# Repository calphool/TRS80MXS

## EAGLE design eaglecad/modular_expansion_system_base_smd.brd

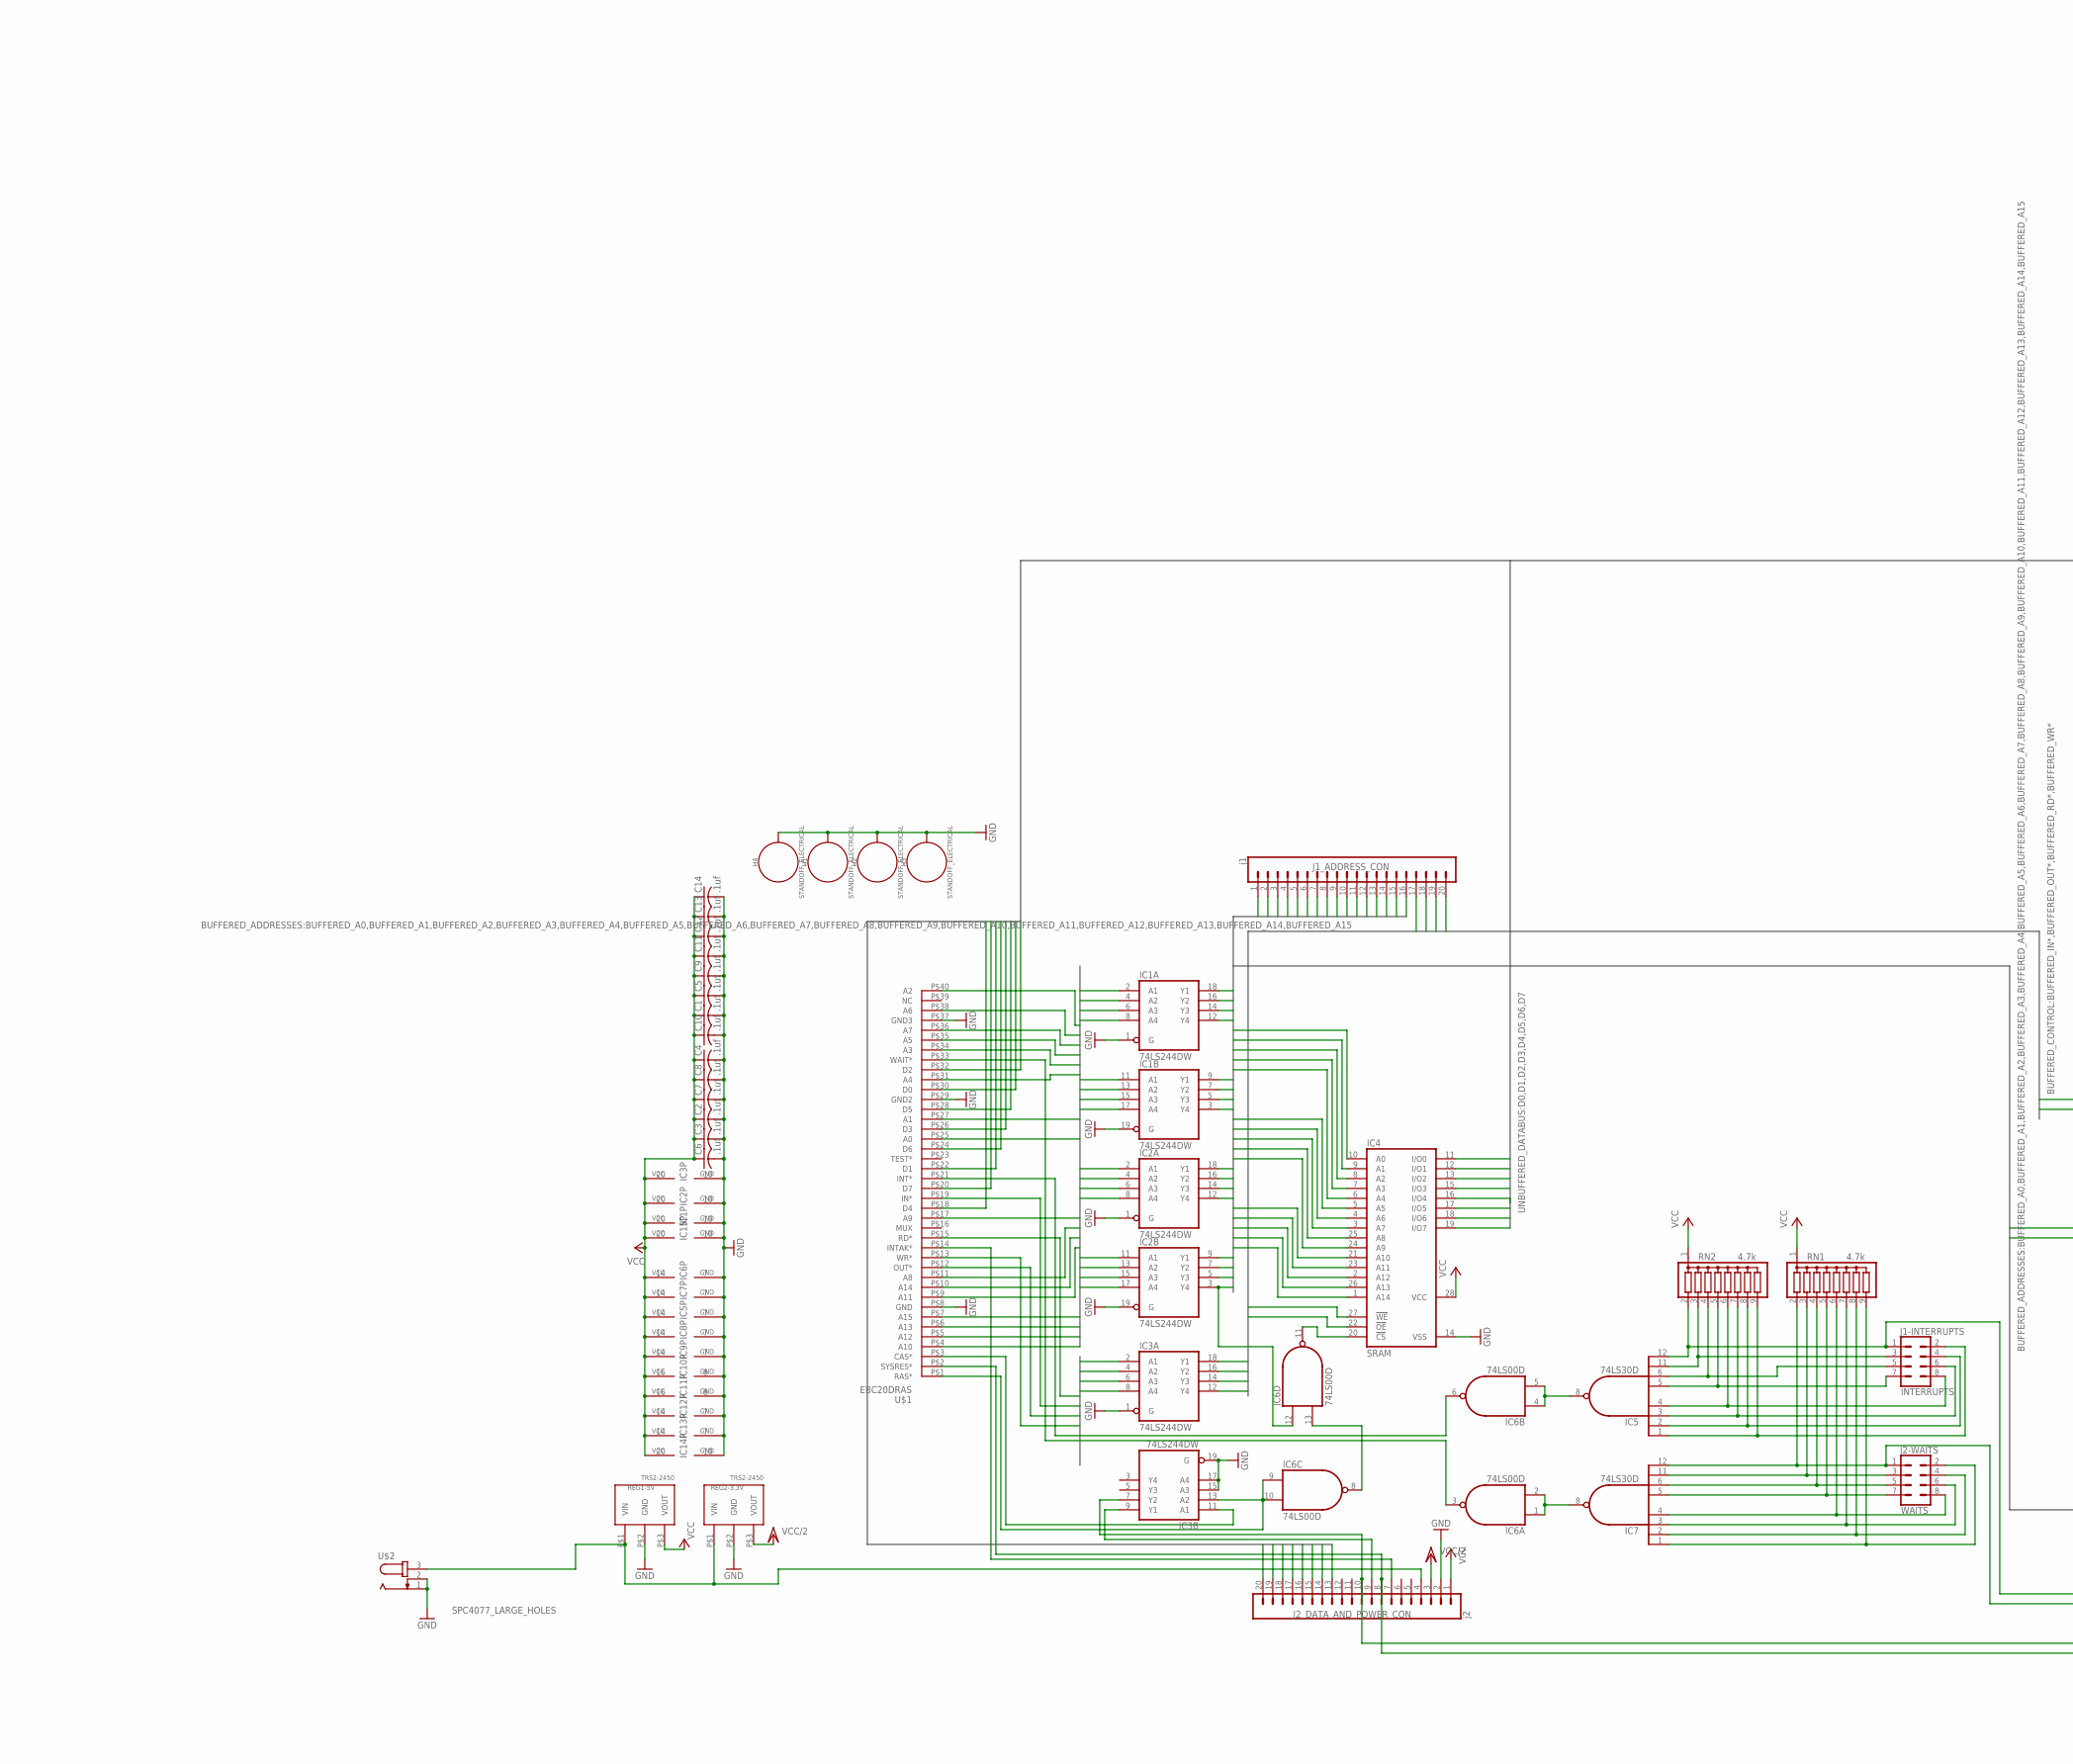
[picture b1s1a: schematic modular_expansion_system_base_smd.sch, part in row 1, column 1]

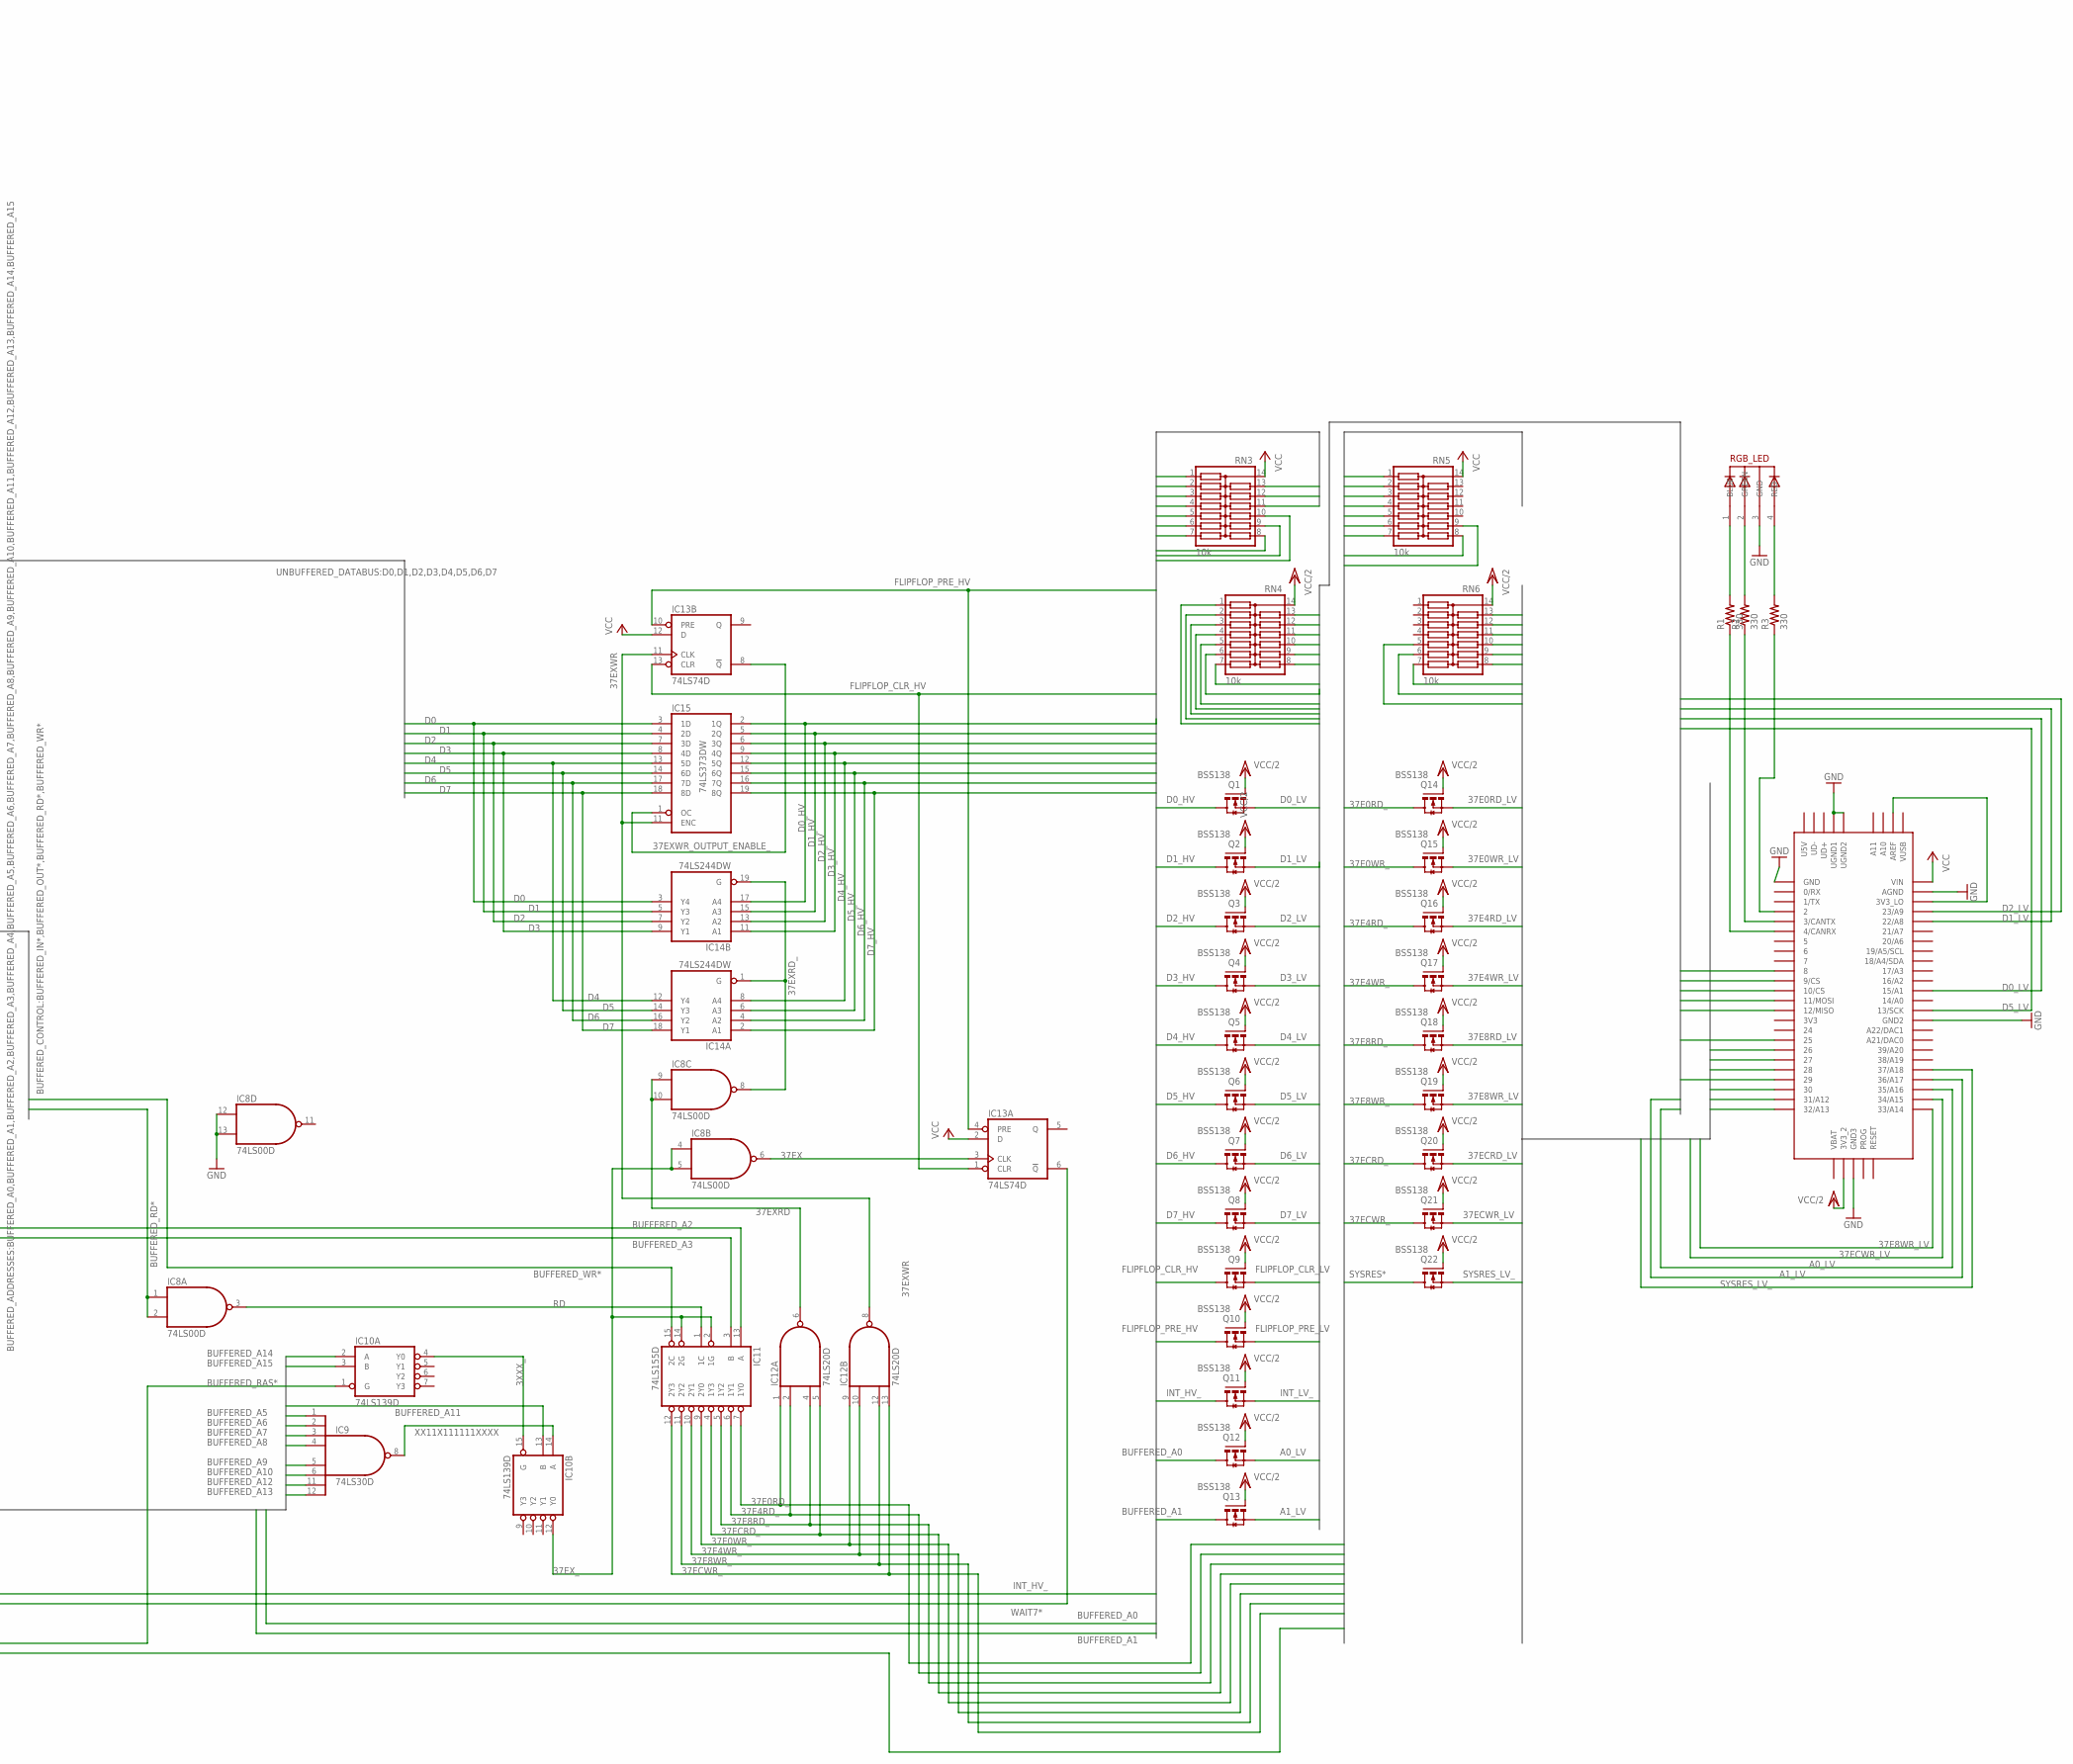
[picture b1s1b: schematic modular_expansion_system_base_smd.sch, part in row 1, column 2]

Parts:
C1, C2, C3, C4, C5, C6, C7, C8, C9, C10, C11, C12, C13, C14: .1uf; C025-025X050
H1, H2, H3, H4: STANDOFF_ELECTRICAL; STANDOFF-ELECTRICAL
IC1, IC2, IC3, IC14: 74LS244DW; SO20W
IC4: SRAM; SO28L
IC5, IC7, IC9: 74LS30D; SO14
IC6, IC8: 74LS00D; SO14
IC10: 74LS139D; SO16
IC11: 74LS155D; SO16
IC12: 74LS20D; SO14
IC13: 74LS74D; SO14
IC15: 74LS373DW; SO20W
J1-INTERRUPTS: INTERRUPTS; 2X4
J1_ADDRESS_CON: j1; 1X20
J2-WAITS: WAITS; 2X4
J2_DATA_AND_POWER_CON: j2; 1X20
Q1, Q2, Q3, Q4, Q5, Q6, Q7, Q8, Q9, Q10, Q11, Q12, Q13, Q14, Q15, Q16, Q17, Q18, Q19, Q20, Q21, Q22: BSS138; SOT23-3
R1, R2, R3: 330; 0207/2V
REG1-5V, REG2-3.3V: TRS2-2450; TRACON_REG
RGB_LED: 5MMRGBLED; LED5MMRGB
RN1, RN2: 4.7k; SIL9
RN3, RN4, RN5, RN6: 10k; SOMC14
U$1: EBC20DRAS
U$2: SPC4077_LARGE_HOLES; SPC4077
U$3: TEENSY_3.5/3.6

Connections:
3XXX_: IC10.4 (Y0), IC10.15 (G)
9V-IN: J2_DATA_AND_POWER_CON.4, REG1-5V.P$1 (VIN), REG2-3.3V.P$1 (VIN), U$2.3
37E0RD_: IC11.7 (1Y0), IC12.1 (I0), Q14.3 (D), RN5.1
37E0RD_LV: Q14.2 (S), RN6.13, U$3.31/A12
37E0WR_: IC11.9 (2Y0), IC12.9 (I0), Q15.3 (D), RN5.2
37E0WR_LV: Q15.2 (S), RN6.12, U$3.27
37E4RD_: IC11.6 (1Y1), IC12.2 (I1), Q16.3 (D), RN5.3
37E4RD_LV: Q16.2 (S), RN6.11, U$3.32/A13
37E4WR_: IC11.10 (2Y1), IC12.10 (I1), Q17.3 (D), RN5.4
37E4WR_LV: Q17.2 (S), RN6.10, U$3.28
37E8RD_: IC11.5 (1Y2), IC12.4 (I2), Q18.3 (D), RN5.5
37E8RD_LV: Q18.2 (S), RN6.9, U$3.30
37E8WR_: IC11.11 (2Y2), IC12.12 (I2), Q19.3 (D), RN5.6
37E8WR_LV: Q19.2 (S), RN6.8, U$3.33/A14
37ECRD_: IC11.4 (1Y3), IC12.5 (I3), Q20.3 (D), RN5.7
37ECRD_LV: Q20.2 (S), RN6.7, U$3.26
37ECWR_: IC11.12 (2Y3), IC12.13 (I3), Q21.3 (D), RN5.8
37ECWR_LV: Q21.2 (S), RN6.6, U$3.34/A15
37EX: IC8.6 (O), IC13.3 (CLK)
37EXRD: IC8.9 (I0), IC8.10 (I1), IC12.6 (O)
37EXRD_: IC8.8 (O), IC14.1 (G), IC14.19 (G)
37EXWR: IC12.8 (O), IC13.11 (CLK), IC15.11 (ENC)
37EXWR_OUTPUT_ENABLE_: IC13.8 (!Q), IC15.1 (OC)
37EX_: IC8.4 (I0), IC8.5 (I1), IC10.12 (Y0), IC11.2 (1G), IC11.14 (2G)
A0: IC1.2 (A1), U$1.P$25 (A0)
A0_LV: Q12.2 (S), RN4.2, U$3.35/A16
A1: IC1.4 (A2), U$1.P$27 (A1)
A1_LV: Q13.2 (S), RN4.1, U$3.36/A17
A2: IC1.6 (A3), U$1.P$40 (A2)
A3: IC1.8 (A4), U$1.P$34 (A3)
A4: IC1.11 (A1), U$1.P$31 (A4)
A5: IC1.13 (A2), U$1.P$35 (A5)
A6: IC1.15 (A3), U$1.P$38 (A6)
A7: IC1.17 (A4), U$1.P$36 (A7)
A8: IC2.2 (A1), U$1.P$11 (A8)
A9: IC2.4 (A2), U$1.P$17 (A9)
A10: IC2.6 (A3), U$1.P$4 (A10)
A11: IC2.8 (A4), U$1.P$9 (A11)
A12: IC2.11 (A1), U$1.P$5 (A12)
A13: IC2.13 (A2), U$1.P$6 (A13)
A14: IC2.15 (A3), U$1.P$10 (A14)
A15: IC2.17 (A4), U$1.P$7 (A15)
A15_AND_RAS: IC4.20 (!CS), IC6.11 (O)
BUFFERED_A0: IC1.18 (Y1), IC4.10 (A0), J1_ADDRESS_CON.1, Q12.3 (D), RN3.12
BUFFERED_A1: IC1.16 (Y2), IC4.9 (A1), J1_ADDRESS_CON.2, Q13.3 (D), RN3.13
BUFFERED_A2: IC1.14 (Y3), IC4.8 (A2), IC11.13 (A), J1_ADDRESS_CON.3
BUFFERED_A3: IC1.12 (Y4), IC4.7 (A3), IC11.3 (B), J1_ADDRESS_CON.4
BUFFERED_A4: IC1.9 (Y1), IC4.6 (A4), J1_ADDRESS_CON.5
BUFFERED_A5: IC1.7 (Y2), IC4.5 (A5), IC9.1 (I0), J1_ADDRESS_CON.6
BUFFERED_A6: IC1.5 (Y3), IC4.4 (A6), IC9.2 (I1), J1_ADDRESS_CON.7
BUFFERED_A7: IC1.3 (Y4), IC4.3 (A7), IC9.3 (I2), J1_ADDRESS_CON.8
BUFFERED_A8: IC2.18 (Y1), IC4.25 (A8), IC9.4 (I3), J1_ADDRESS_CON.9
BUFFERED_A9: IC2.16 (Y2), IC4.24 (A9), IC9.5 (I4), J1_ADDRESS_CON.10
BUFFERED_A10: IC2.14 (Y3), IC4.21 (A10), IC9.6 (I5), J1_ADDRESS_CON.11
BUFFERED_A11: IC2.12 (Y4), IC4.23 (A11), IC10.13 (B), J1_ADDRESS_CON.12
BUFFERED_A12: IC2.9 (Y1), IC4.2 (A12), IC9.11 (I6), J1_ADDRESS_CON.13
BUFFERED_A13: IC2.7 (Y2), IC4.26 (A13), IC9.12 (I7), J1_ADDRESS_CON.14
BUFFERED_A14: IC2.5 (Y3), IC4.1 (A14), IC10.2 (A), J1_ADDRESS_CON.15
BUFFERED_A15: IC2.3 (Y4), IC6.12 (I0), IC10.3 (B), J1_ADDRESS_CON.16
BUFFERED_CAS*: IC3.9 (Y1), J2_DATA_AND_POWER_CON.9
BUFFERED_IN*: IC3.14 (Y3), J1_ADDRESS_CON.17
BUFFERED_OUT*: IC3.12 (Y4), J1_ADDRESS_CON.18
BUFFERED_RAS*: IC3.7 (Y2), IC10.1 (G), J2_DATA_AND_POWER_CON.10
BUFFERED_RD*: IC3.18 (Y1), IC4.22 (!OE), IC8.1 (I0), IC8.2 (I1), J1_ADDRESS_CON.19
BUFFERED_WR*: IC3.16 (Y2), IC4.27 (!WE), IC11.15 (2C), J1_ADDRESS_CON.20
CAS*: IC3.11 (A1), U$1.P$3 (CAS*)
D0: IC4.11 (I/O0), IC14.3 (Y4), IC15.3 (1D), J2_DATA_AND_POWER_CON.20, U$1.P$30 (D0)
D0_HV: IC14.17 (A4), IC15.2 (1Q), Q1.3 (D), RN3.1
D0_LV: Q1.2 (S), RN4.13, U$3.15/A1
D1: IC4.12 (I/O1), IC14.5 (Y3), IC15.4 (2D), J2_DATA_AND_POWER_CON.19, U$1.P$22 (D1)
D1_HV: IC14.15 (A3), IC15.5 (2Q), Q2.3 (D), RN3.2
D1_LV: Q2.2 (S), RN4.12, U$3.22/A8
D2: IC4.13 (I/O2), IC14.7 (Y2), IC15.7 (3D), J2_DATA_AND_POWER_CON.18, U$1.P$32 (D2)
D2_HV: IC14.13 (A2), IC15.6 (3Q), Q3.3 (D), RN3.3
D2_LV: Q3.2 (S), RN4.11, U$3.23/A9
D3: IC4.15 (I/O3), IC14.9 (Y1), IC15.8 (4D), J2_DATA_AND_POWER_CON.17, U$1.P$26 (D3)
D3_HV: IC14.11 (A1), IC15.9 (4Q), Q4.3 (D), RN3.4
D3_LV: Q4.2 (S), RN4.10, U$3.9/CS
D4: IC4.16 (I/O4), IC14.12 (Y4), IC15.13 (5D), J2_DATA_AND_POWER_CON.16, U$1.P$18 (D4)
D4_HV: IC14.8 (A4), IC15.12 (5Q), Q5.3 (D), RN3.5
D4_LV: Q5.2 (S), RN4.9, U$3.10/CS
D5: IC4.17 (I/O5), IC14.14 (Y3), IC15.14 (6D), J2_DATA_AND_POWER_CON.15, U$1.P$28 (D5)
D5_HV: IC14.6 (A3), IC15.15 (6Q), Q6.3 (D), RN3.6
D5_LV: Q6.2 (S), RN4.8, U$3.13/SCK
D6: IC4.18 (I/O6), IC14.16 (Y2), IC15.17 (7D), J2_DATA_AND_POWER_CON.14, U$1.P$24 (D6)
D6_HV: IC14.4 (A2), IC15.16 (7Q), Q7.3 (D), RN3.7
D6_LV: Q7.2 (S), RN4.7, U$3.11/MOSI
D7: IC4.19 (I/O7), IC14.18 (Y1), IC15.18 (8D), J2_DATA_AND_POWER_CON.13, U$1.P$20 (D7)
D7_HV: IC14.2 (A1), IC15.19 (8Q), Q8.3 (D), RN3.8
D7_LV: Q8.2 (S), RN4.6, U$3.12/MISO
FLIPFLOP_CLR_HV: IC13.1 (CLR), IC13.13 (CLR), Q9.3 (D), RN3.9
FLIPFLOP_CLR_LV: Q9.2 (S), RN4.5, U$3.25
FLIPFLOP_PRE_HV: IC13.4 (PRE), IC13.10 (PRE), Q10.3 (D), RN3.10
FLIPFLOP_PRE_LV: Q10.2 (S), RN4.4, U$3.29
GND: C1.2, C2.2, C3.2, C4.2, C5.2, C6.2, C7.2, C8.2, C9.2, C10.2, C11.2, C12.2, C13.2, C14.2, H1.P1, H2.P1, H3.P1, H4.P1, IC1.1 (G), IC1.10 (GND), IC1.19 (G), IC2.1 (G), IC2.10 (GND), IC2.19 (G), IC3.1 (G), IC3.10 (GND), IC3.15 (A3), IC3.17 (A4), IC3.19 (G), IC4.14 (VSS), IC5.7 (GND), IC6.7 (GND), IC7.7 (GND), IC8.7 (GND), IC8.12 (I0), IC8.13 (I1), IC9.7 (GND), IC10.8 (GND), IC11.8 (GND), IC12.7 (GND), IC13.7 (GND), IC14.10 (GND), IC15.10 (GND), J2_DATA_AND_POWER_CON.2, REG1-5V.P$2 (GND), REG2-3.3V.P$2 (GND), RGB_LED.3 (GND), U$1.P$8 (GND), U$1.P$29 (GND2), U$1.P$37 (GND3), U$2.1, U$2.2, U$3.AGND, U$3.GND, U$3.GND2, U$3.GND3, U$3.UGND1, U$3.UGND2
IN*: IC3.6 (A3), U$1.P$19 (IN*)
INT: IC5.8 (O), IC6.4 (I0), IC6.5 (I1)
INT1*: IC5.11 (I6), J1-INTERRUPTS.3, RN2.3
INT2*: IC5.6 (I5), J1-INTERRUPTS.5, RN2.4
INT3*: IC5.5 (I4), J1-INTERRUPTS.7, RN2.5
INT4*: IC5.1 (I0), J1-INTERRUPTS.2, RN2.9
INT5*: IC5.2 (I1), J1-INTERRUPTS.4, RN2.8
INT6*: IC5.3 (I2), J1-INTERRUPTS.6, RN2.7
INT7*: IC5.4 (I3), J1-INTERRUPTS.8, RN2.6
INT*: IC6.6 (O), U$1.P$21 (INT*)
INTAK*: J2_DATA_AND_POWER_CON.7, U$1.P$14 (INTAK*)
INT_HV_: IC5.12 (I7), J1-INTERRUPTS.1, Q11.3 (D), RN2.2, RN3.11
INT_LV_: Q11.2 (S), RN4.3, U$3.8
unnamed: U$3.3V3_LO, U$3.AREF
unnamed: R1.2, RGB_LED.1 (BLUE)
unnamed: R2.2, RGB_LED.2 (GREEN)
unnamed: R3.2, RGB_LED.4 (RED)
unnamed: R3.1, U$3.2
unnamed: R2.1, U$3.3/CANTX
unnamed: R1.1, U$3.4/CANRX
OUT*: IC3.8 (A4), U$1.P$12 (OUT*)
RAS: IC6.8 (O), IC6.13 (I1)
RAS*: IC3.13 (A2), IC6.9 (I0), IC6.10 (I1), U$1.P$1 (RAS*)
RD: IC8.3 (O), IC11.1 (1C)
RD*: IC3.2 (A1), U$1.P$15 (RD*)
SYSRES*: J2_DATA_AND_POWER_CON.8, Q22.3 (D), RN5.9, U$1.P$2 (SYSRES*)
SYSRES_LV_: Q22.2 (S), RN6.5, U$3.37/A18
VCC: C1.1, C2.1, C3.1, C4.1, C5.1, C6.1, C7.1, C8.1, C9.1, C10.1, C11.1, C12.1, C13.1, C14.1, IC1.20 (VCC), IC2.20 (VCC), IC3.20 (VCC), IC4.28 (VCC), IC5.14 (VCC), IC6.14 (VCC), IC7.14 (VCC), IC8.14 (VCC), IC9.14 (VCC), IC10.16 (VCC), IC11.16 (VCC), IC12.14 (VCC), IC13.2 (D), IC13.12 (D), IC13.14 (VCC), IC14.20 (VCC), IC15.20 (VCC), J2_DATA_AND_POWER_CON.1, REG1-5V.P$3 (VOUT), RN1.1, RN2.1, RN3.14, RN5.14, U$3.VIN
VCC/2: J2_DATA_AND_POWER_CON.3, Q1.1 (G), Q2.1 (G), Q3.1 (G), Q4.1 (G), Q5.1 (G), Q6.1 (G), Q7.1 (G), Q8.1 (G), Q9.1 (G), Q10.1 (G), Q11.1 (G), Q12.1 (G), Q13.1 (G), Q14.1 (G), Q15.1 (G), Q16.1 (G), Q17.1 (G), Q18.1 (G), Q19.1 (G), Q20.1 (G), Q21.1 (G), Q22.1 (G), REG2-3.3V.P$3 (VOUT), RN4.14, RN6.14, U$3.3V3_2
WAIT: IC6.1 (I0), IC6.2 (I1), IC7.8 (O)
WAIT0*: IC7.4 (I3), J2-WAITS.8, RN1.6
WAIT1*: IC7.3 (I2), J2-WAITS.6, RN1.7
WAIT2*: IC7.2 (I1), J2-WAITS.4, RN1.8
WAIT3*: IC7.1 (I0), J2-WAITS.2, RN1.9
WAIT4*: IC7.5 (I4), J2-WAITS.7, RN1.5
WAIT5*: IC7.6 (I5), J2-WAITS.5, RN1.4
WAIT6*: IC7.11 (I6), J2-WAITS.3, RN1.3
WAIT7*: IC7.12 (I7), IC13.6 (!Q), J2-WAITS.1, RN1.2
WAIT*: IC6.3 (O), U$1.P$33 (WAIT*)
WR*: IC3.4 (A2), U$1.P$13 (WR*)
XX11X111111XXXX: IC9.8 (O), IC10.14 (A)

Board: 2 copper layers, 74 parts (8 on the bottom side), 136 nets, no tracks yet.

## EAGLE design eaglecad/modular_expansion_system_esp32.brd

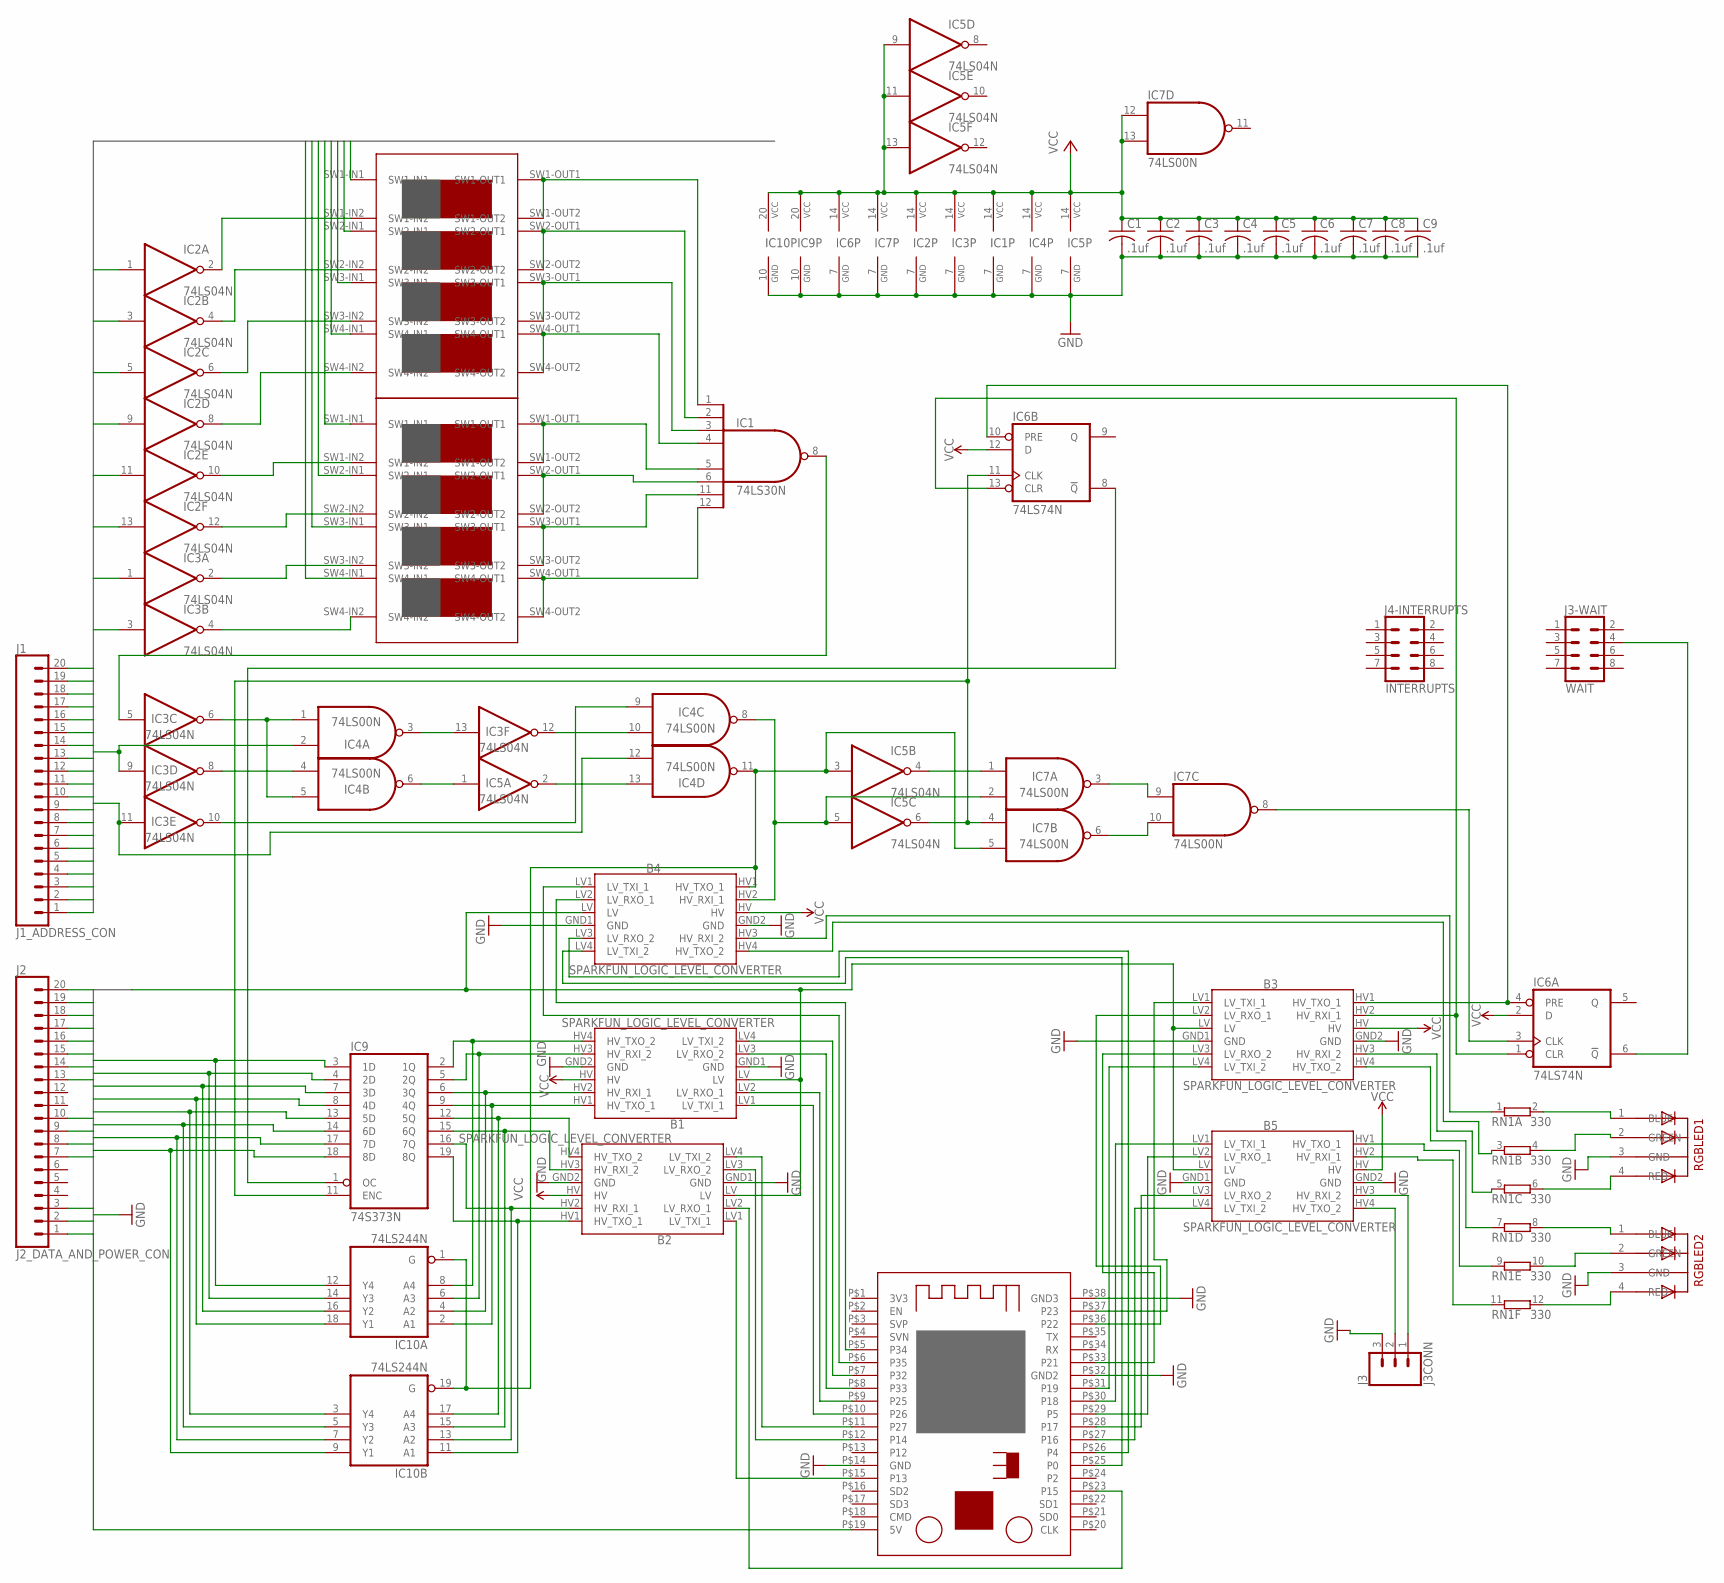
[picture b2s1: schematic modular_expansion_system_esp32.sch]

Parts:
B1, B2, B3, B4, B5: SPARKFUN_LOGIC_LEVEL_CONVERTER
C1, C2, C3, C4, C5, C6, C7, C8, C9: .1uf; C025-025X050
IC1: 74LS30N; DIL14
IC2, IC3, IC5: 74LS04N; DIL14
IC4, IC7: 74LS00N; DIL14
IC6: 74LS74N; DIL14
IC9: 74S373N; DIL20
IC10: 74LS244N; DIL20
J1: J1_ADDRESS_CON; 1X20
J2: J2_DATA_AND_POWER_CON; 1X20
J3: J3CONN; 1X03
J3-WAIT: WAIT; 2X4
J4-INTERRUPTS: INTERRUPTS; 2X4
RGBLED1, RGBLED2: 5MMRGBLED; LED5MMRGB
RN1: 330; SIL12
SW1, SW2: CTS206-124
U$1: ESP32S

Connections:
A0: IC3.3 (I), J1.1, SW1.SW4-IN1
A0_OR_NOT_A0: IC1.12 (I7), SW1.SW4-OUT1, SW1.SW4-OUT2
A1: IC3.1 (I), J1.2, SW1.SW3-IN1
A1_OR_NOT_A1: IC1.11 (I6), SW1.SW3-OUT1, SW1.SW3-OUT2
A2: IC2.13 (I), J1.3, SW1.SW2-IN1
A2_OR_NOT_A2: IC1.6 (I5), SW1.SW2-OUT1, SW1.SW2-OUT2
A3: IC2.11 (I), J1.4, SW1.SW1-IN1
A3_OR_NOT_A3: IC1.5 (I4), SW1.SW1-OUT1, SW1.SW1-OUT2
A4: IC2.9 (I), J1.5, SW2.SW4-IN1
A4_OR_NOT_A4: IC1.4 (I3), SW2.SW4-OUT1, SW2.SW4-OUT2
A5: IC2.5 (I), J1.6, SW2.SW3-IN1
A5_OR_NOT_A5: IC1.3 (I2), SW2.SW3-OUT1, SW2.SW3-OUT2
A6: IC2.3 (I), J1.7, SW2.SW2-IN1
A6_OR_NOT_A6: IC1.2 (I1), SW2.SW2-OUT1, SW2.SW2-OUT2
A7: IC2.1 (I), J1.8, SW2.SW1-IN1
A7_OR_NOT_A7: IC1.1 (I0), SW2.SW1-OUT1, SW2.SW1-OUT2
A8: J1.9
A9: J1.10
A10: J1.11
A11: J1.12
A12: J1.13
A13: J1.14
A14: J1.15
A15: J1.16
ADDRESS_SELECTED: IC3.6 (O), IC4.1 (I0), IC4.5 (I1)
ADDRESS_SELECTED_: IC1.8 (O), IC3.5 (I)
CAS*: J2.9
D0: IC9.18 (8D), IC10.9 (Y1), J2.20
D0_HV: B2.HV1 (HV_TXO_1), IC9.19 (8Q), IC10.11 (A1)
D0_LV: B2.LV1 (LV_TXI_1), U$1.P$15 (P13)
D1: IC9.17 (7D), IC10.7 (Y2), J2.19
D1_HV: B2.HV2 (HV_RXI_1), IC9.16 (7Q), IC10.13 (A2)
D1_LV: B2.LV2 (LV_RXO_1), U$1.P$23 (P15)
D2: IC9.14 (6D), IC10.5 (Y3), J2.18
D2_HV: B2.HV3 (HV_RXI_2), IC9.15 (6Q), IC10.15 (A3)
D2_LV: B2.LV3 (LV_RXO_2), U$1.P$12 (P14)
D3: IC9.13 (5D), IC10.3 (Y4), J2.17
D3_HV: B2.HV4 (HV_TXO_2), IC9.12 (5Q), IC10.17 (A4)
D3_LV: B2.LV4 (LV_TXI_2), U$1.P$11 (P27)
D4: IC9.8 (4D), IC10.18 (Y1), J2.16
D4_HV: B1.HV1 (HV_TXO_1), IC9.9 (4Q), IC10.2 (A1)
D4_LV: B1.LV1 (LV_TXI_1), U$1.P$10 (P26)
D5: IC9.7 (3D), IC10.16 (Y2), J2.15
D5_HV: B1.HV2 (HV_RXI_1), IC9.6 (3Q), IC10.4 (A2)
D5_LV: B1.LV2 (LV_RXO_1), U$1.P$9 (P25)
D6: IC9.4 (2D), IC10.14 (Y3), J2.14
D6_HV: B1.HV3 (HV_RXI_2), IC9.5 (2Q), IC10.6 (A3)
D6_LV: B1.LV3 (LV_RXO_2), U$1.P$8 (P33)
D7: IC9.3 (1D), IC10.12 (Y4), J2.13
D7_HV: B1.HV4 (HV_TXO_2), IC9.2 (1Q), IC10.8 (A4)
D7_LV: B1.LV4 (LV_TXI_2), U$1.P$7 (P32)
GND: B1.GND1 (GND), B1.GND2 (GND), B2.GND1 (GND), B2.GND2 (GND), B3.GND1 (GND), B3.GND2 (GND), B4.GND1 (GND), B4.GND2 (GND), B5.GND1 (GND), B5.GND2 (GND), C1.2, C2.2, C3.2, C4.2, C5.2, C6.2, C7.2, C8.2, C9.2, IC1.7 (GND), IC2.7 (GND), IC3.7 (GND), IC4.7 (GND), IC5.7 (GND), IC6.7 (GND), IC7.7 (GND), IC9.10 (GND), IC10.10 (GND), J2.2, J3.3, RGBLED1.3 (GND), RGBLED2.3 (GND), U$1.P$14 (GND), U$1.P$32 (GND2), U$1.P$38 (GND3)
IC6A_CLR_LV: B3.LV2 (LV_RXO_1), U$1.P$36 (P22)
IC6A_PRE_LV: B3.LV1 (LV_TXI_1), U$1.P$37 (P23)
IC6_CLR_HV: B3.HV2 (HV_RXI_1), IC6.1 (CLR), IC6.13 (CLR)
IC6_PRE_HV: B3.HV1 (HV_TXO_1), IC6.4 (PRE), IC6.10 (PRE)
IN: IC3.8 (O), IC4.4 (I0)
INTAK*: J2.7
IN_: IC3.9 (I), IC4.2 (I1), J1.17
unnamed: IC3.13 (I), IC4.3 (O)
unnamed: IC4.6 (O), IC5.1 (I)
unnamed: IC3.12 (O), IC4.10 (I1)
unnamed: IC4.13 (I1), IC5.2 (O)
unnamed: IC7.3 (O), IC7.9 (I0)
unnamed: IC7.6 (O), IC7.10 (I1)
unnamed: B5.LV3 (LV_RXO_2), U$1.P$28 (P17)
unnamed: B5.LV4 (LV_TXI_2), U$1.P$27 (P16)
unnamed: B5.HV3 (HV_RXI_2), J3.1
unnamed: B5.HV4 (HV_TXO_2), J3.2
NOT_A0: IC3.4 (O), SW1.SW4-IN2
NOT_A1: IC3.2 (O), SW1.SW3-IN2
NOT_A2: IC2.12 (O), SW1.SW2-IN2
NOT_A3: IC2.10 (O), SW1.SW1-IN2
NOT_A4: IC2.8 (O), SW2.SW4-IN2
NOT_A5: IC2.6 (O), SW2.SW3-IN2
NOT_A6: IC2.4 (O), SW2.SW2-IN2
NOT_A7: IC2.2 (O), SW2.SW1-IN2
OUT: IC3.10 (O), IC4.9 (I0)
OUT_: IC3.11 (I), IC4.12 (I0), J1.18
RAS*: J2.10
RD*: J1.19
RGBLED1_B: RGBLED1.1 (BLUE), RN1.2
RGBLED1_B_5V: B4.HV3 (HV_RXI_2), RN1.1
RGBLED1_B_LV: B4.LV3 (LV_RXO_2), U$1.P$26 (P4)
RGBLED1_G: RGBLED1.2 (GREEN), RN1.4 (2)
RGBLED1_G_5V: B4.HV4 (HV_TXO_2), RN1.3 (1)
RGBLED1_G_LV: B4.LV4 (LV_TXI_2), U$1.P$25 (P0)
RGBLED1_R: RGBLED1.4 (RED), RN1.6 (2)
RGBLED1_R_5V: B3.HV3 (HV_RXI_2), RN1.5 (1)
RGBLED1_R_LV: B3.LV3 (LV_RXO_2), U$1.P$33 (P21)
RGBLED2_B: RGBLED2.1 (BLUE), RN1.8 (2)
RGBLED2_B_5V: B3.HV4 (HV_TXO_2), RN1.7 (1)
RGBLED2_B_LV: B3.LV4 (LV_TXI_2), U$1.P$31 (P19)
RGBLED2_G: RGBLED2.2 (GREEN), RN1.10 (2)
RGBLED2_G_5V: B5.HV1 (HV_TXO_1), RN1.9 (1)
RGBLED2_G_LV: B5.LV1 (LV_TXI_1), U$1.P$30 (P18)
RGBLED2_R: RGBLED2.4 (RED), RN1.12 (2)
RGBLED2_R_5V: B5.HV2 (HV_RXI_1), RN1.11 (1)
RGBLED2_R_LV: B5.LV2 (LV_RXO_1), U$1.P$29 (P5)
SYSRES*: J2.8
VCC: B1.HV, B2.HV, B3.HV, B4.HV, B5.HV, C1.1, C2.1, C3.1, C4.1, C5.1, C6.1, C7.1, C8.1, C9.1, IC1.14 (VCC), IC2.14 (VCC), IC3.14 (VCC), IC4.14 (VCC), IC5.9 (I), IC5.11 (I), IC5.13 (I), IC5.14 (VCC), IC6.2 (D), IC6.12 (D), IC6.14 (VCC), IC7.12 (I0), IC7.13 (I1), IC7.14 (VCC), IC9.20 (VCC), IC10.20 (VCC), J2.1, U$1.P$19 (5V)
VCC/2: B1.LV, B2.LV, B3.LV, B4.LV, B5.LV, J2.3
WAIT_: IC6.6 (!Q), J3-WAIT.4
WIFI_IN: IC5.4 (O), IC7.1 (I0)
WIFI_IN_: B4.HV1 (HV_TXO_1), IC4.11 (O), IC5.3 (I), IC7.5 (I1), IC10.1 (G), IC10.19 (G)
WIFI_IN_LV_: B4.LV1 (LV_TXI_1), U$1.P$6 (P35)
WIFI_IN_OR_OUT: IC6.3 (CLK), IC7.8 (O)
WIFI_OUT: IC5.6 (O), IC6.11 (CLK), IC7.4 (I0), IC9.11 (ENC)
WIFI_OUT_: B4.HV2 (HV_RXI_1), IC4.8 (O), IC5.5 (I), IC7.2 (I1)
WIFI_OUT_LV_: B4.LV2 (LV_RXO_1), U$1.P$5 (P34)
WIFI_OUT_OUTPUT_ENABLE_: IC6.8 (!Q), IC9.1 (OC)
WR*: J1.20

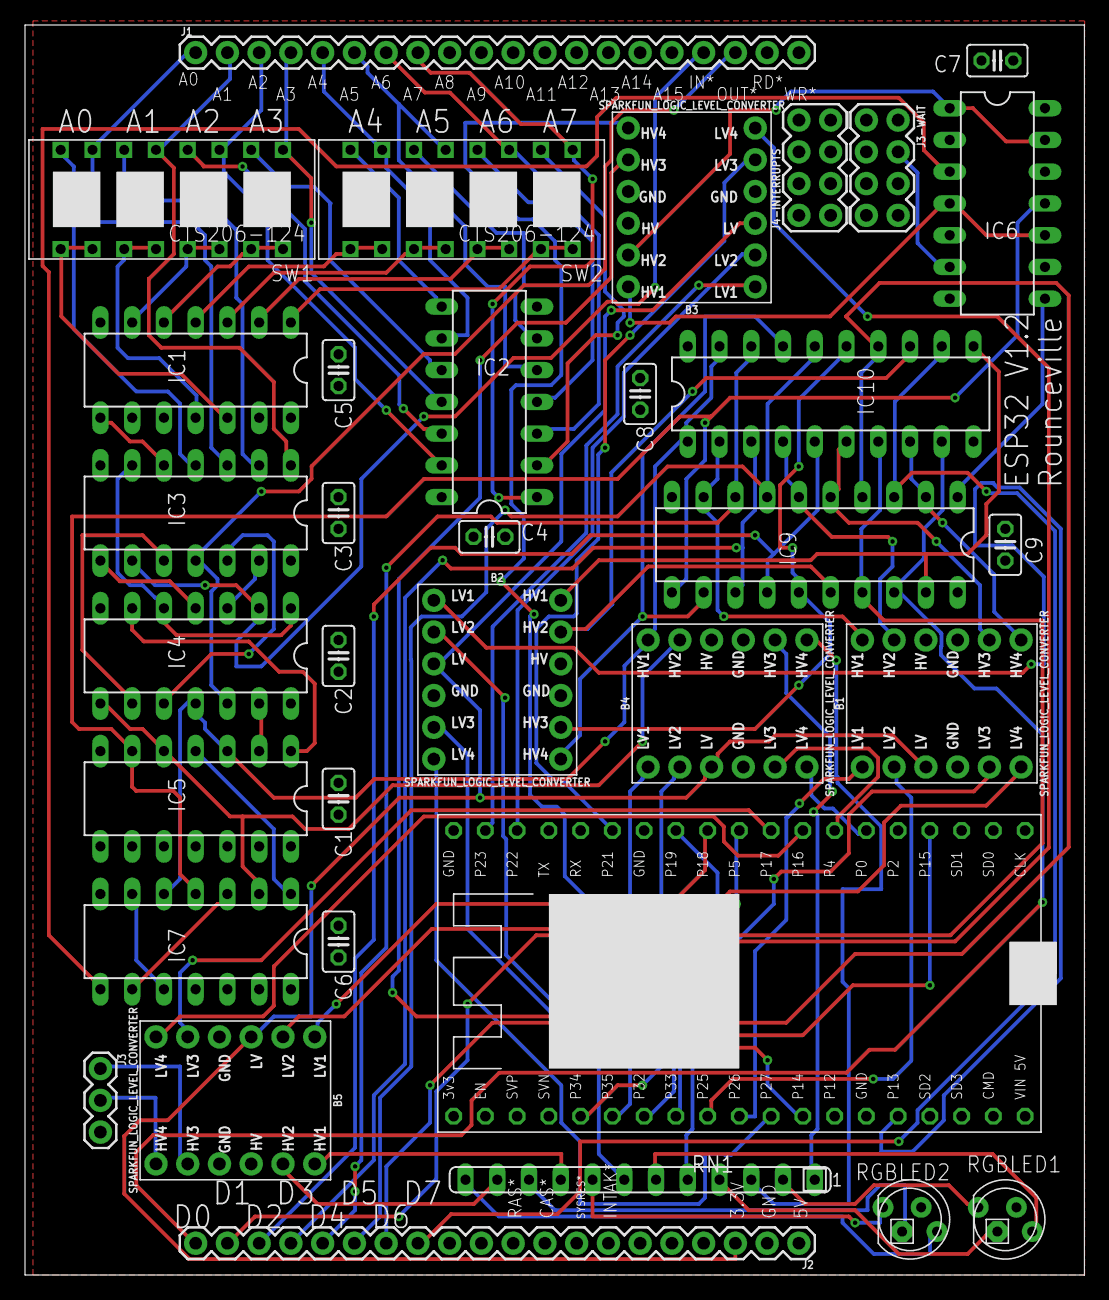
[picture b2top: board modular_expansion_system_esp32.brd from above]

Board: 2 copper layers, 84.8 x 100.0 mm, 34 parts (0 on the bottom side), 98 nets.

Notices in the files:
eaglecad/modular_expansion_system_base_smd.brd:
Joe Rounceville (C) 2020
parts and their libraries:
SparkFun-Connectors: Licensing: Creative Commons ShareAlike 4.0 International - https://creativecommons.org/licenses/by-sa/4.0
